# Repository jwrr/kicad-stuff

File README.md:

KiCad Readme
------------

Notes
------

* How to rename a project?
  * #run from gitbash
  * cp -rf jwrr-003 jwrr-004
  * cd jwrr-004
  * mv jwrr-003.pro jwrr-004.pro
  * mv jwrr-003.sch jwrr-004.pro
  * mv jwrr-003.kicad_pcb jwrr-004.kicad_pcb
  * sed -i 's#003#004#g' jwrr-004.kicad_*

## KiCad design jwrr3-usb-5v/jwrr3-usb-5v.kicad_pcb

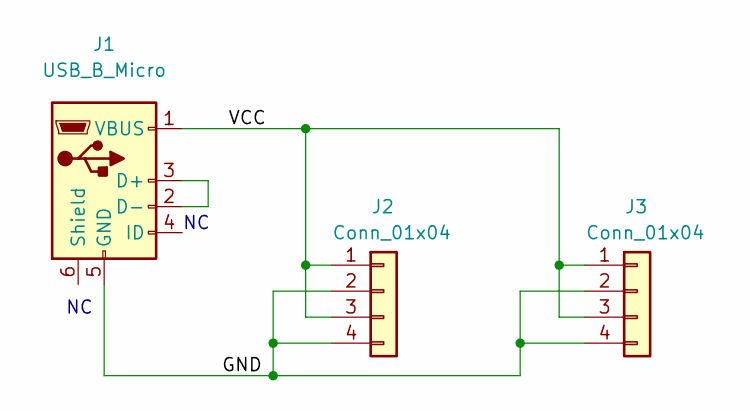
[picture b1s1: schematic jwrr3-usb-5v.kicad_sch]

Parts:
J1: USB_B_Micro; USB_Micro-B_Wuerth_614105150721_Vertical
J2, J3: Conn_01x04; PinHeader_1x04_P2.54mm_Vertical

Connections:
/GND: J1.5 (GND), J2.2, J2.4, J3.2, J3.4
/VCC: J1.1 (VBUS), J2.1, J2.3, J3.1, J3.3
unnamed: J1.2 (D-), J1.3 (D+)

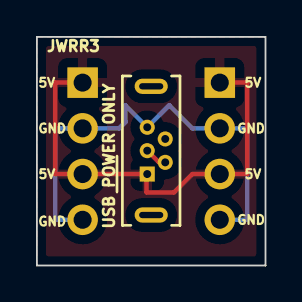
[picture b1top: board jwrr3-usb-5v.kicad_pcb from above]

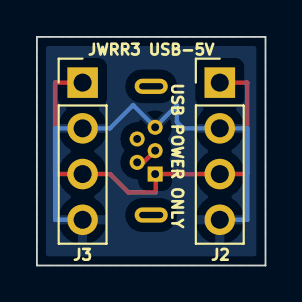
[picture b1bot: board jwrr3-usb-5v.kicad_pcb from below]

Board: 2 copper layers, 12.7 x 12.7 mm, 3 parts (2 on the bottom side), 3 nets.

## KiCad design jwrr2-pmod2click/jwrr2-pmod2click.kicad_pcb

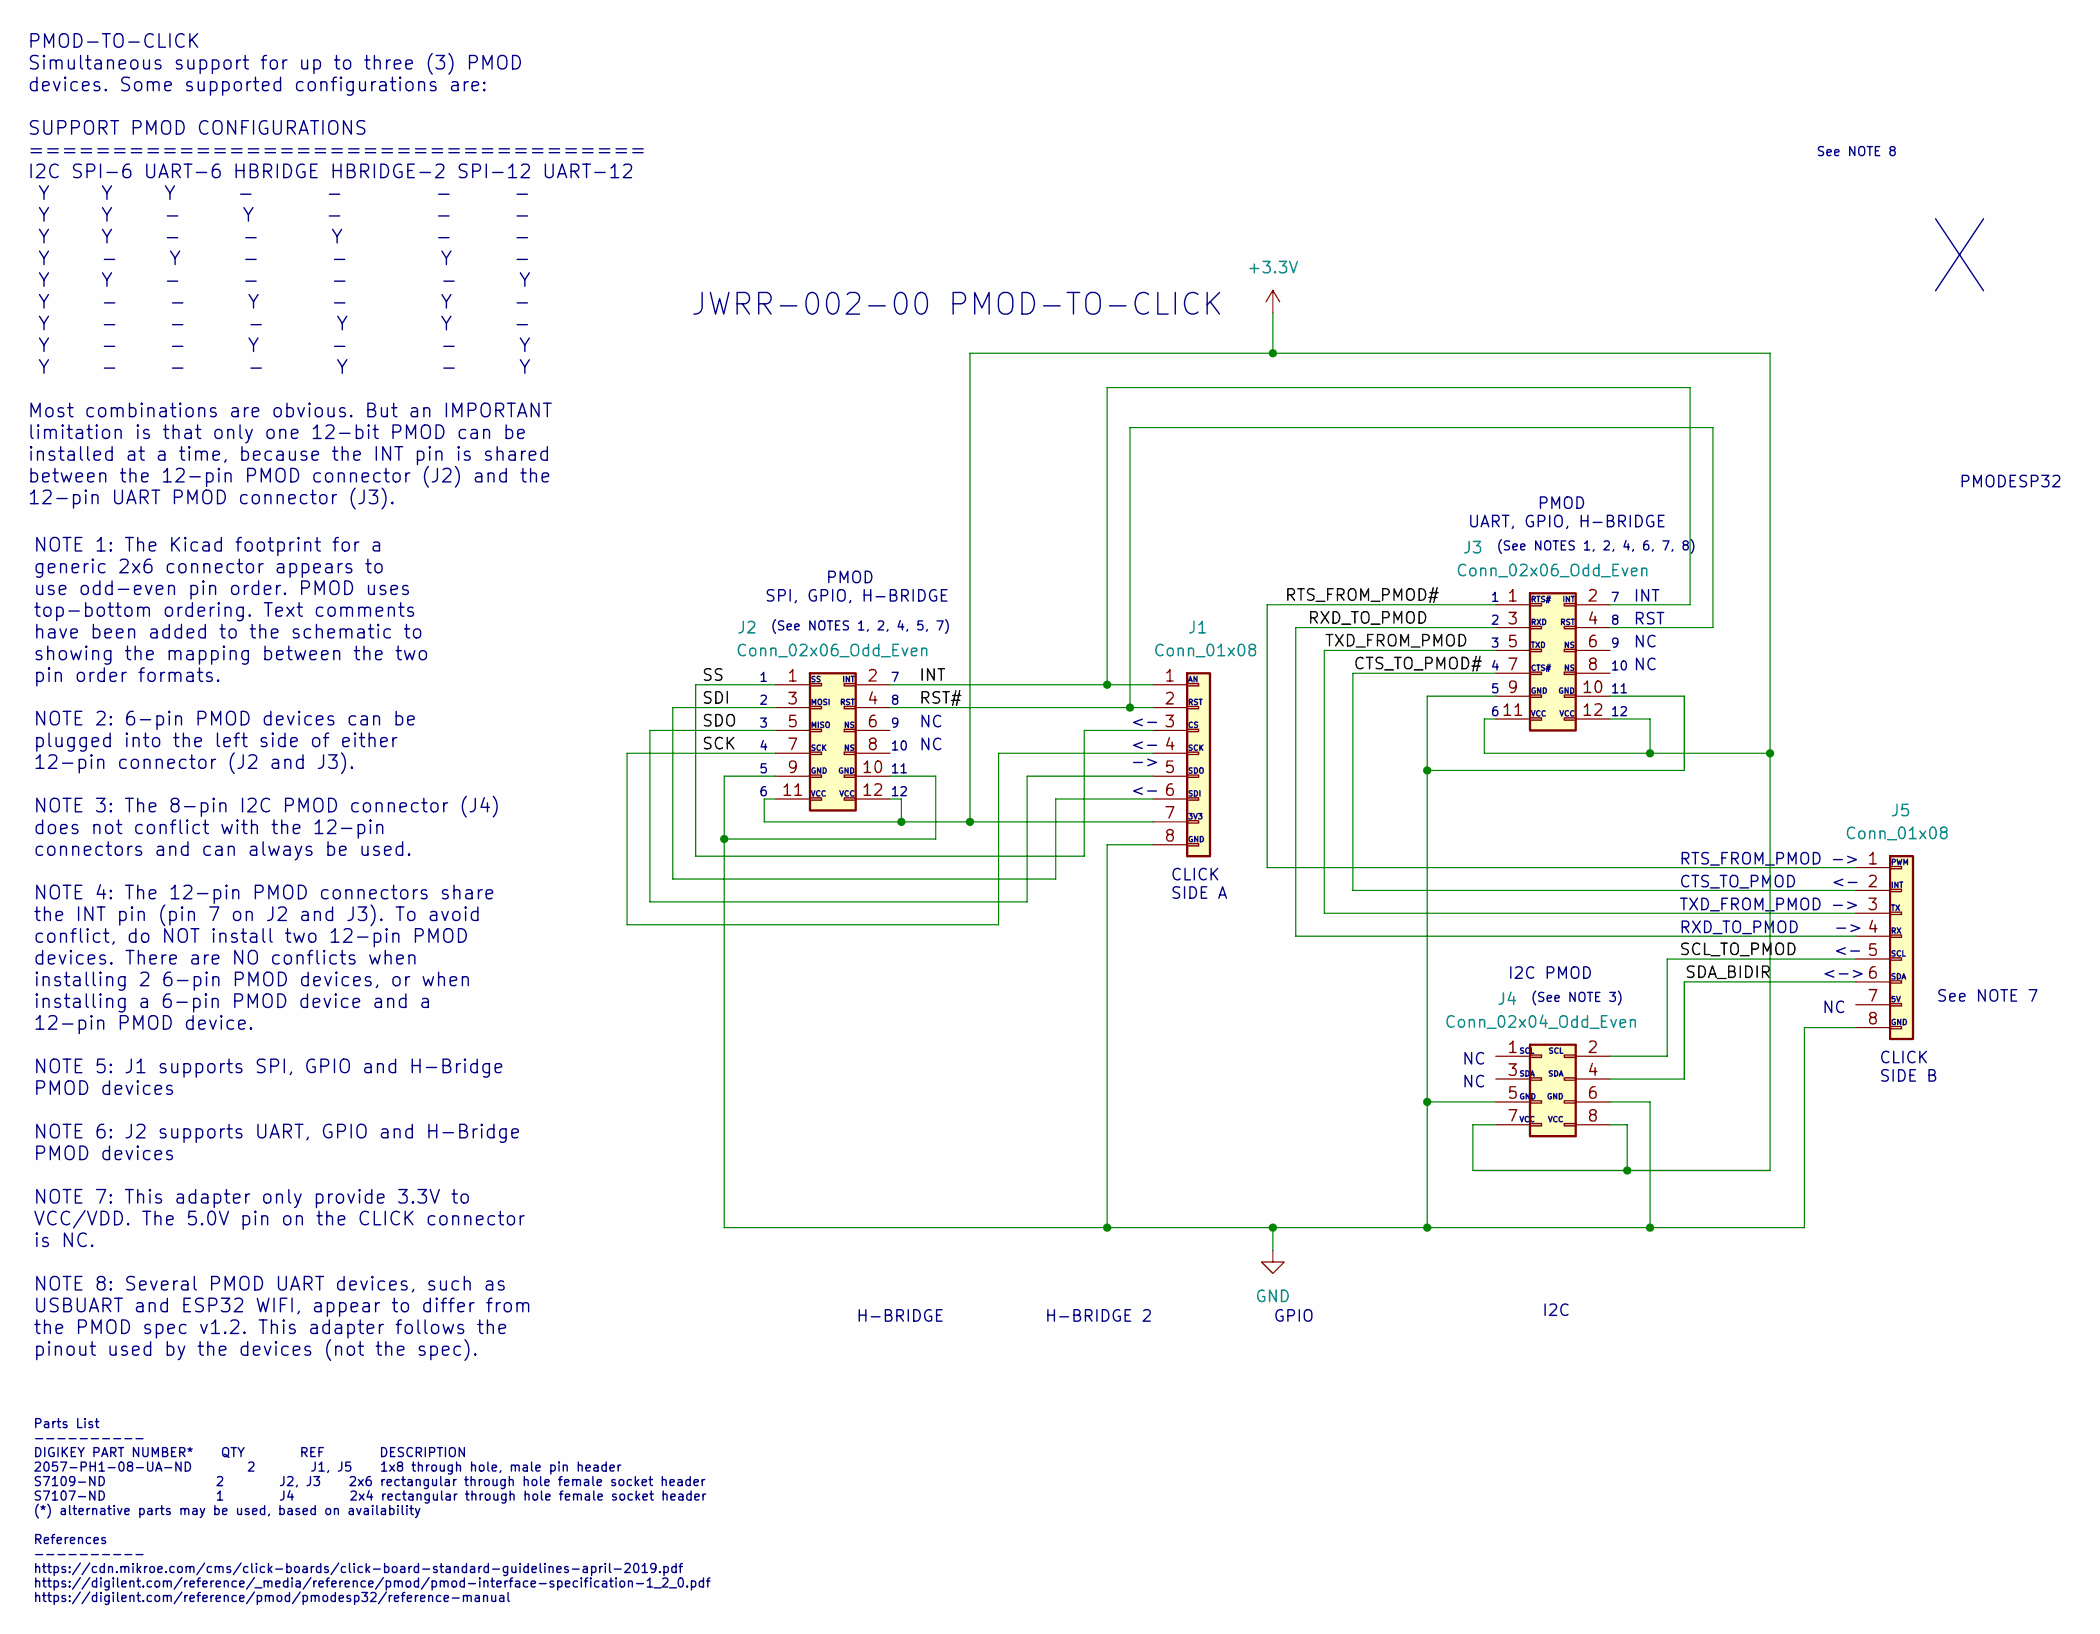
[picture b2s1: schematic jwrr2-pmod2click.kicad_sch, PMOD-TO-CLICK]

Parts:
J1, J5: Conn_01x08; PinHeader_1x08_P2.54mm_Vertical
J2, J3: Conn_02x06_Odd_Even; PinSocket_2x06_P2.54mm_Vertical
J4: Conn_02x04_Odd_Even; PinSocket_2x04_P2.54mm_Vertical

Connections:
+3V3: J1.7, J2.11, J2.12, J3.11, J3.12, J4.7, J4.8
/CTS_TO_PMOD#: J3.7, J5.2
/INT: J1.1, J2.2, J3.2
/RST#: J1.2, J2.4, J3.4
/RTS_FROM_PMOD#: J3.1, J5.1
/RXD_TO_PMOD: J3.3, J5.4
/SCK: J1.4, J2.7
/SCL_TO_PMOD: J4.2, J5.5
/SDA_BIDIR: J4.4, J5.6
/SDI: J1.6, J2.3
/SDO: J1.5, J2.5
/SS: J1.3, J2.1
/TXD_FROM_PMOD: J3.5, J5.3
GND: J1.8, J2.9, J2.10, J3.9, J3.10, J4.5, J4.6, J5.8

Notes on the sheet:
RXD
GPIO
JWRR-002-00 PMOD-TO-CLICK
H-BRIDGE 2
SCL
CLICK SIDE B
(See NOTES 1, 2, 4, 5, 7)
PMOD SPI, GPIO, H-BRIDGE
RST
H-BRIDGE
PMOD-TO-CLICK Simultaneous support for up to three (3) PMOD devices. Some supported configurations are: SUPPORT PMOD CONFIGURATIONS ===================================== I2C SPI-6 UART-6 HBRIDGE HBRIDGE-2 SPI-12 UART-12 Y Y Y - - - - Y Y - Y - - - Y Y - - Y - - Y - Y - - Y - Y Y - - - - Y Y - - Y -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
TXD_FROM_PMOD ->
PMODESP32
VCC
GND
Parts List ---------- DIGIKEY PART NUMBER* QTY REF DESCRIPTION 2057-PH1-08-UA-ND 2 J1, J5 1x8 through hole, male pin header S7109-ND 2 J2, J3 2x6 rectangular through hole female socket header S7107-ND 1 J4 2x4 rectangular through hole female socket header (*) alternative parts may be used, based on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
SCK
SDA
<->
See NOTE 7
See NOTE 8
INT
TXD
PWM
RTS#
CLICK SIDE A
CTS_TO_PMOD <-
MOSI
I2C
SDO
(See NOTE 3)
MISO
3V3
NOTE 1: The Kicad footprint for a generic 2x6 connector appears to use odd-even pin order. PMOD uses top-bottom ordering. Text comments have been added to the schematic to showing the mapping between the two pin order formats. NOTE 2: 6-pin PMOD devices can be plugged into the left side of either 1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
I2C PMOD
RTS_FROM_PMOD ->
(See NOTES 1, 2, 4, 6, 7, 8)
RXD_TO_PMOD ->
CTS#
SDI

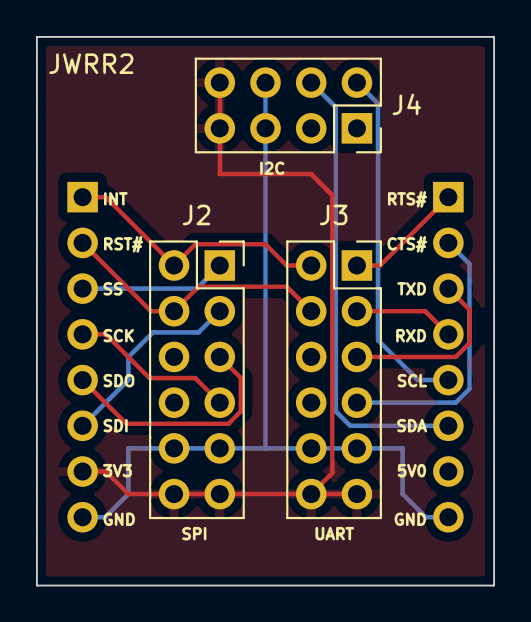
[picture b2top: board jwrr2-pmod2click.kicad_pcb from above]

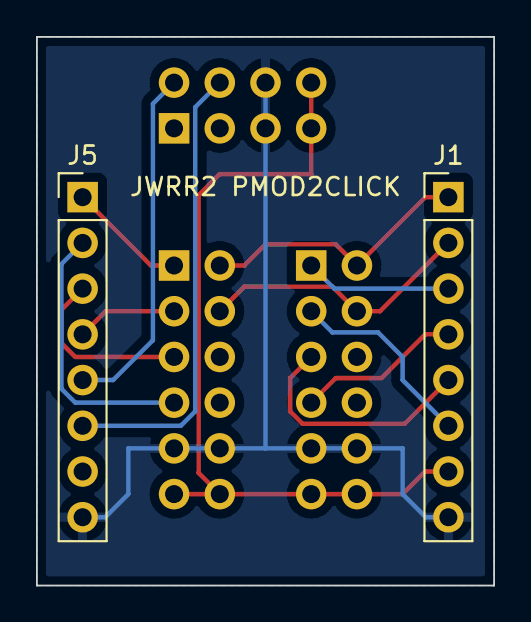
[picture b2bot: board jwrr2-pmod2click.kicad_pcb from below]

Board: 2 copper layers, 25.4 x 30.5 mm, 5 parts (2 on the bottom side), 14 nets.

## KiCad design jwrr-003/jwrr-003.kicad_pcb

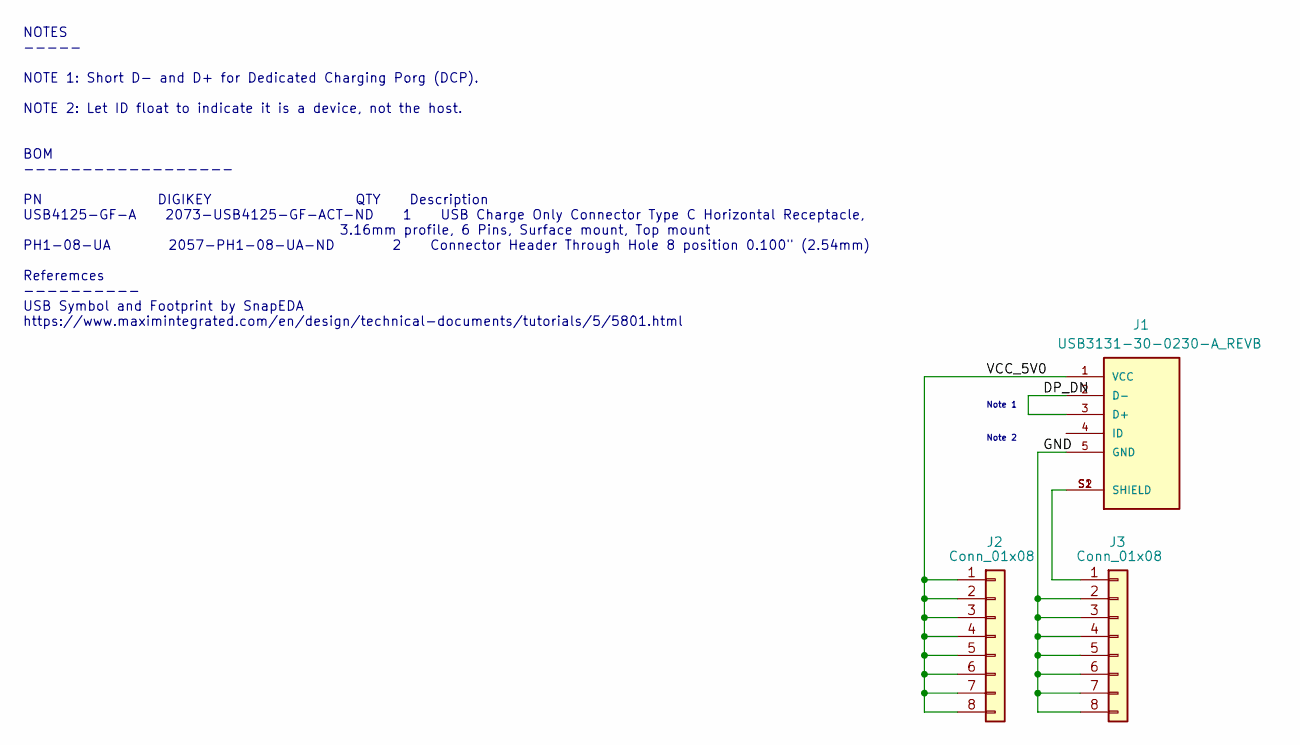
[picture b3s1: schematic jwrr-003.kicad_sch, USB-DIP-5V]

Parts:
J1: USB3131-30-0230-A_REVB; GCT_USB3131-30-0230-A_REVB; PARTREV B4
J2, J3: Conn_01x08; PinHeader_1x08_P2.54mm_Vertical

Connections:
/DP_DN: J1.2 (D-), J1.3 (D+)
/GND: J1.5 (GND), J3.2, J3.3, J3.4, J3.5, J3.6, J3.7, J3.8
/VCC_5V0: J1.1 (VCC), J2.1, J2.2, J2.3, J2.4, J2.5, J2.6, J2.7, J2.8
unnamed: J1.S1 (SHIELD), J1.S2 (SHIELD), J3.1

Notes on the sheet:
Note 1
NOTES ----- NOTE 1: Short D- and D+ for Dedicated Charging Porg (DCP). NOTE 2: Let ID float to indicate it is a device, not the host. BOM ------------------ PN DIGIKEY QTY Description USB4125-GF-A 2073-USB4125-GF-ACT-ND 1 USB Charge Only Connector Type C Horizontal Receptacle, 3.16mm profile, 6 Pin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
Note 2

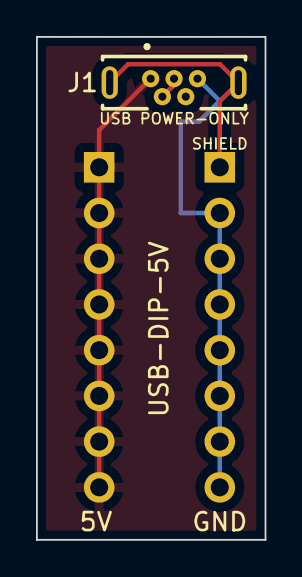
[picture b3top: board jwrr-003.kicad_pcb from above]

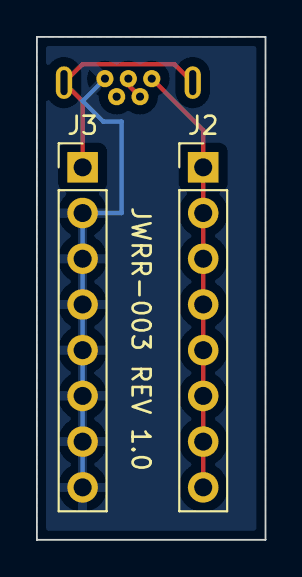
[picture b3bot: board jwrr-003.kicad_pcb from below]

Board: 2 copper layers, 12.7 x 27.9 mm, 3 parts (2 on the bottom side), 4 nets.

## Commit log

2022-02-19 jwrr-001
2022-02-19 jwrr-001 - add readme
2022-02-19 jwrr-oo1 - Tweak readme markdown
2022-02-20 jwrr-002 - pmod-to-click
2022-02-21 jwrr-003 usb-dip-5v
2022-02-22 readme
2022-02-22 readme markdown cleanup
2022-02-22 readme again'
2022-03-21 jwrr001 fabbed at dkred and working. jwrr2,3,6 set to jlcpcb
